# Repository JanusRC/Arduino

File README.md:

Janus Arduino Library
===

www.janus-rc.com

Janus Arduino repository for shield hardware and software references. 
The Janus Plugin Arduino Shield is fully compatible with the Arduino Uno and Leonardo currently.

This library should aid in getting a proof of concept with the Janus Plug in Modems done extremely 
quickly, allowing application development to focus on the bigger picture.

### Hardware
Arduino Shield and accessories - Designed in EAGLE 7.3.0

* `Plugin Shield v2.0`: Arduino Shield - Tested for the Uno/Leonardo
* `Eagle Library`: Janus Eagle Library

### Software
Janus software library for the Arduino platform, with example demos for standard M2M/IoT implementations.

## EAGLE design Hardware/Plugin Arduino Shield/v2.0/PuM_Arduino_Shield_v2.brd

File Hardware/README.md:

Janus Arduino Library - Hardware
===

www.janus-rc.com

Janus Arduino hardware repository. Contains board designs for shields and accessories.

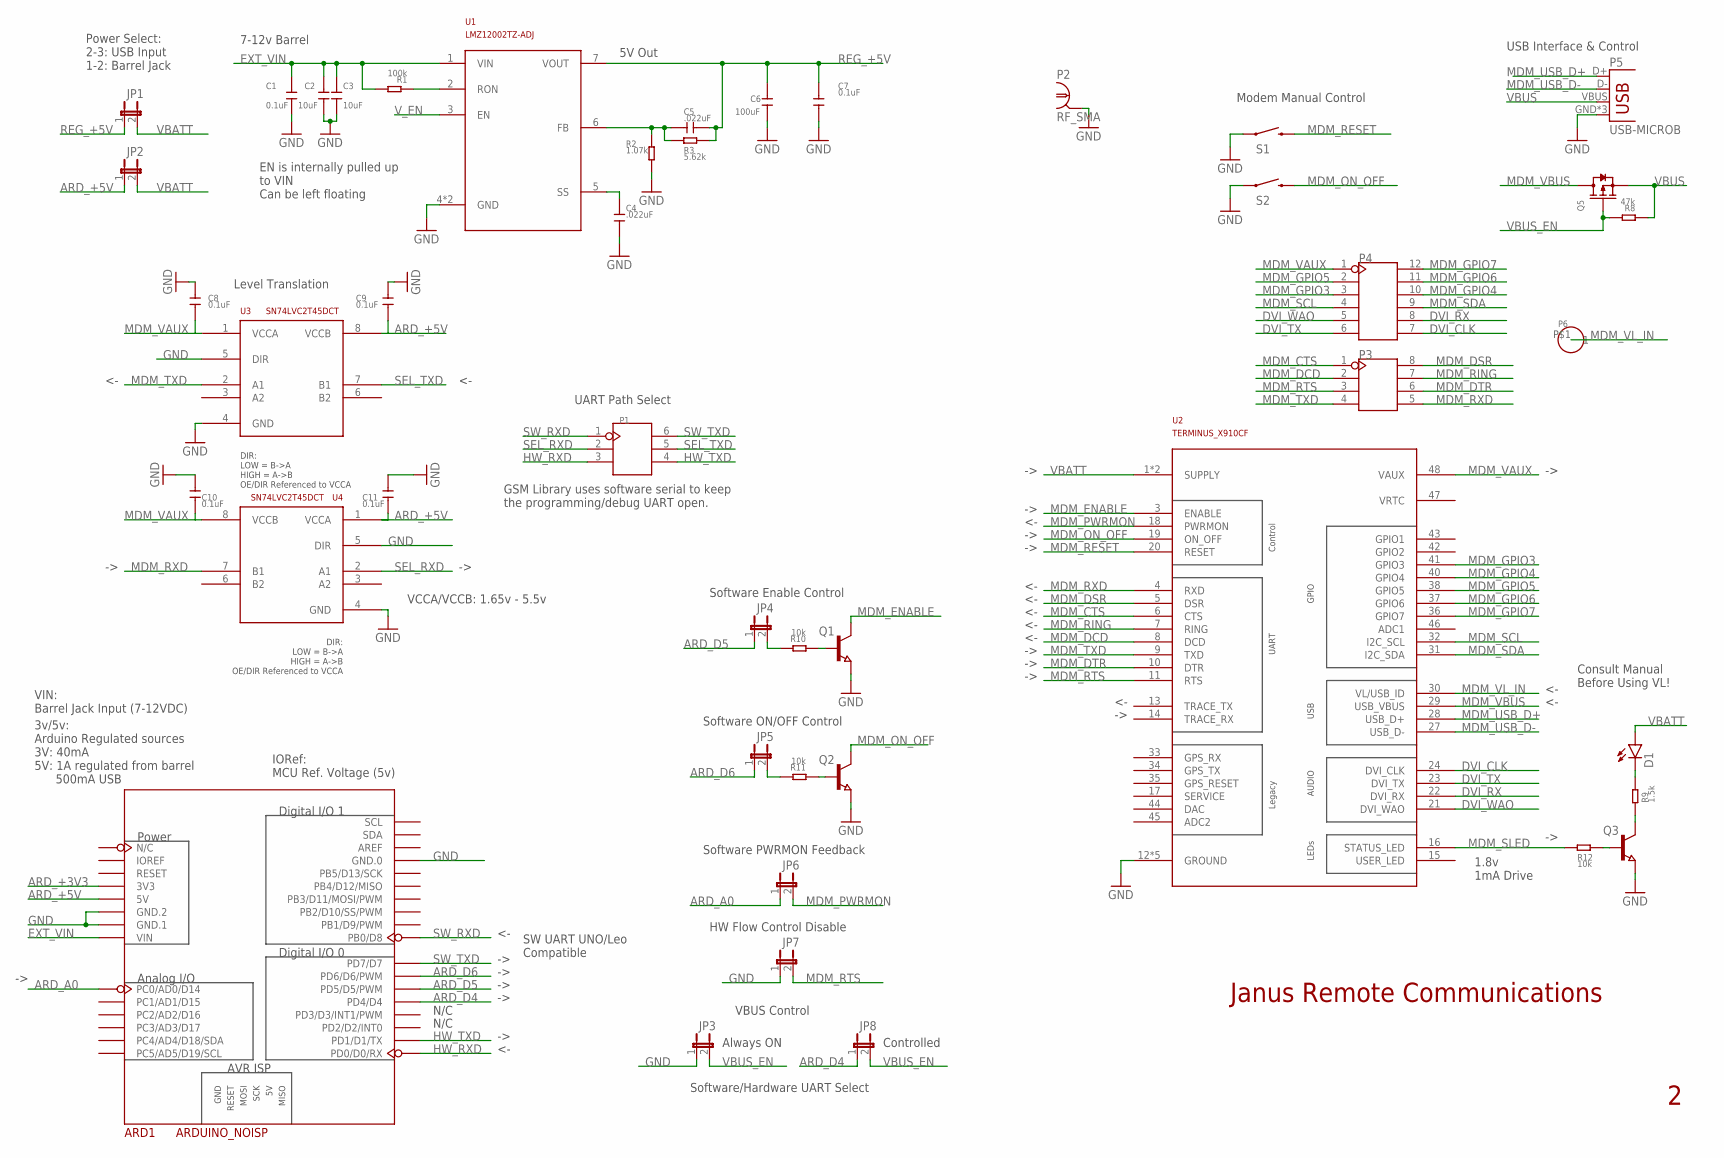
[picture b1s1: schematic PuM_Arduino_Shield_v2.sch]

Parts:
ARD1: ARDUINO_NOISP
C1, C7, C8, C9, C10, C11: 0.1uF; C0402
C2, C3: 10uF; C0805
C4, C5: .022uF; C0402
C6: 100uF; C1206
D1: LED0603; LED-0603
JP1, JP4, JP5, JP6, JP7, JP8: JUMPER-2SMD-NC; SJ_2S
JP2, JP3: JUMPER-2SMD-NO; SJ_2S-NO
P1: HEADER-2X3P-2.54; 2X3P-2.54
P2: RF_SMA; RF_SMA_NOPIN
P3: HEADER-2X4P-2.54; 2X4P-2.54
P4: HEADER-2X6P-2.54; 2X6P-2.54
P5: USB-MICROB
P6: HEADER-1P-35; 1P-65/35MIL
Q1, Q2, Q3: NPN-TRANSISTOR_SOT23; SOT23
Q5: MOSFET-P'SI2323CDS/SI2305DS<BR>'; SOT23
R1: 100k; R0402
R2: 1.07k; R0402
R3: 5.62k; R0402
R8: 47k; R0402
R9: 1.5k; R0402
R10, R11, R12: 10k; R0402
S1, S2: SWITCH-MOMENTARY-2SIDE_EZ; TACTILE-PTH-SIDEEZ
U1: LMZ12002TZ-ADJ; TO-PMOD-7
U2: TERMINUS_X910CF; X910CF
U3, U4: SN74LVC2T45DCT; LSSOP-8

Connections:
ARD_+3V3: ARD1.3V3
ARD_+5V: ARD1.5V, C9.1, C11.1, JP2.1, U3.8 (VCCB), U4.1 (VCCA)
ARD_A0: ARD1.A0 (PC0/AD0/D14), JP6.1
ARD_D4: ARD1.D4 (PD4/D4), JP8.1
ARD_D5: ARD1.D5 (PD5/D5/PWM), JP4.1
ARD_D6: ARD1.D6 (PD6/D6/PWM), JP5.1
DVI_CLK: P4.7, U2.24 (DVI_CLK)
DVI_RX: P4.8, U2.22 (DVI_RX)
DVI_TX: P4.6, U2.23 (DVI_TX)
DVI_WAO: P4.5, U2.21 (DVI_WAO)
EXT_VIN: ARD1.VIN, C1.2, C2.2, C3.2, R1.2, U1.1 (VIN)
GND: ARD1.GND0 (GND.0), ARD1.GND1 (GND.1), ARD1.GND2 (GND.2), C1.1, C2.1, C3.1, C4.1, C6.1, C7.1, C8.2, C9.2, C10.2, C11.2, JP3.1, JP7.1, P2.2, P2.3, P2.4, P2.5, P5.GND, P5.MT1 (GND), P5.MT2 (GND), Q1.2 (E), Q2.2 (E), Q3.2 (E), R2.2, S1.1, S2.1, U1.4 (GND), U1.EP (GND), U2.12 (GROUND), U2.25 (GROUND), U2.26 (GROUND), U2.39 (GROUND), U2.49 (GROUND), U3.4 (GND), U3.5 (DIR), U4.4 (GND), U4.5 (DIR)
HW_RXD: ARD1.D0 (PD0/D0/RX), P1.3
HW_TXD: ARD1.D1 (PD1/D1/TX), P1.4
MDM_CTS: P3.1, U2.6 (CTS)
MDM_DCD: P3.2, U2.8 (DCD)
MDM_DSR: P3.8, U2.5 (DSR)
MDM_DTR: P3.6, U2.10 (DTR)
MDM_ENABLE: Q1.3 (C), U2.3 (ENABLE)
MDM_GPIO3: P4.3, U2.41 (GPIO3)
MDM_GPIO4: P4.10, U2.40 (GPIO4)
MDM_GPIO5: P4.2, U2.38 (GPIO5)
MDM_GPIO6: P4.11, U2.37 (GPIO6)
MDM_GPIO7: P4.12, U2.36 (GPIO7)
MDM_ON_OFF: Q2.3 (C), S2.2, U2.19 (ON_OFF)
MDM_PWRMON: JP6.2, U2.18 (PWRMON)
MDM_RESET: S1.2, U2.20 (RESET)
MDM_RING: P3.7, U2.7 (RING)
MDM_RTS: JP7.2, P3.3, U2.11 (RTS)
MDM_RXD: P3.5, U2.4 (RXD), U4.7 (B1)
MDM_SCL: P4.4, U2.32 (I2C_SCL)
MDM_SDA: P4.9, U2.31 (I2C_SDA)
MDM_SLED: R12.2, U2.16 (STATUS_LED)
MDM_TXD: P3.4, U2.9 (TXD), U3.2 (A1)
MDM_USB_D+: P5.D+, U2.28 (USB_D+)
MDM_USB_D-: P5.D-, U2.27 (USB_D-)
MDM_VAUX: C8.1, C10.1, P4.1, U2.48 (VAUX), U3.1 (VCCA), U4.8 (VCCB)
MDM_VBUS: Q5.3 (D), U2.29 (USB_VBUS)
MDM_VL_IN: P6.P$1, U2.30 (VL/USB_ID)
unnamed: Q3.3 (C), R9.2
unnamed: JP5.2, R11.1
unnamed: R1.1, U1.2 (RON)
unnamed: C4.2, U1.5 (SS)
unnamed: C5.1, R2.1, R3.2, U1.6 (FB)
unnamed: D1.C, R9.1
unnamed: JP4.2, R10.1
unnamed: Q1.1 (B), R10.2
unnamed: Q2.1 (B), R11.2
unnamed: Q3.1 (B), R12.1
REG_+5V: C5.2, C6.2, C7.2, JP1.1, R3.1, U1.7 (VOUT)
SEL_RXD: P1.2, U4.2 (A1)
SEL_TXD: P1.5, U3.7 (B1)
SW_RXD: ARD1.D8 (PB0/D8), P1.1
SW_TXD: ARD1.D7 (PD7/D7), P1.6
VBATT: D1.A, JP1.2, JP2.2, U2.1 (SUPPLY), U2.2 (SUPPLY)
VBUS: P5.VBUS, Q5.2 (S), R8.2
VBUS_EN: JP3.2, JP8.2, Q5.1 (G), R8.1
V_EN: U1.3 (EN)

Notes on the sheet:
VIN: Barrel Jack Input (7-12VDC)
3v/5v: Arduino Regulated sources 3V: 40mA 5V: 1A regulated from barrel 500mA USB
IORef: MCU Ref. Voltage (5v)
GSM Library uses software serial to keep the programming/debug UART open.
EN is internally pulled up to VIN Can be left floating
7-12v Barrel
5V Out
Level Translation
Modem Manual Control
USB Interface & Control
Software ON/OFF Control
Software/Hardware UART Select
Software Enable Control
Software PWRMON Feedback
HW Flow Control Disable
Power Select: 2-3: USB Input 1-2: Barrel Jack
VBUS Control
Always ON
Controlled
N/C
SW UART UNO/Leo Compatible
Consult Manual Before Using VL!
1.8v 1mA Drive
UART Path Select
VCCA/VCCB: 1.65v - 5.5v
Janus Remote Communications

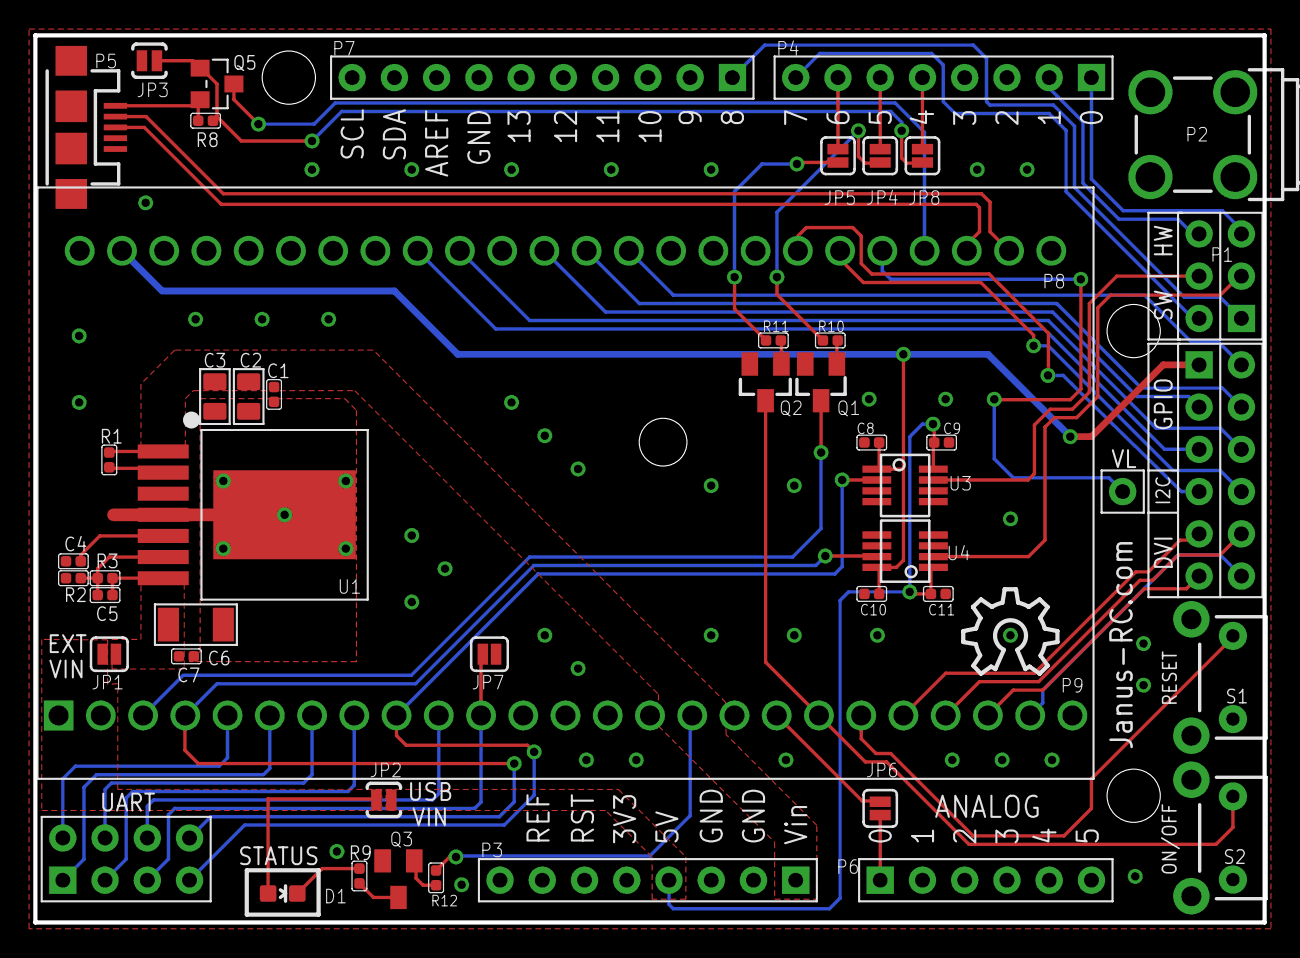
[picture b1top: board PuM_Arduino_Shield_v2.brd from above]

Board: 2 copper layers, 73.9 x 53.3 mm, 47 parts (0 on the bottom side), 56 nets.

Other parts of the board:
DRILEGEND: DRILEGEND
U$2: OSHW_10X200_NOTEXT

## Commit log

2015-09-24 :confetti_ball: Added .gitattributes & .gitignore files
2015-09-24 Janus Arduino Library
2015-09-24 Adjusted readme
2015-10-15 Updated board design and library
2015-12-22 Update Baudrate_Change.ino
    Change pin #defines & fix baud rate
2015-12-22 Update Modem_Information.ino
    Change pin #defines
2015-12-22 Update Modem_Terminal.ino
    Change pin #defines
2015-12-22 Update Modem_USBControl.ino
    Change pin #defines
2015-12-22 Update SMS_Echo.ino
    Change pin #defines
2015-12-22 Update Socket_Dial.ino
    Change pin #defines
2015-12-22 Update Socket_Listen.ino
    Change pin #defines
2016-05-18 Remote_Control_Using_SMS_Commands
    This arduino program allows you to control the devices (LED, Buzzer, LCD) attached to Arduino GPIO pins using commands sent through an SMS.

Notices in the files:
parts and their libraries:
SparkFun-Connectors: Licensing: Creative Commons ShareAlike 4.0 International - https://creativecommons.org/licenses/by-sa/4.0
